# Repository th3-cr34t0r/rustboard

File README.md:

# RUSTBOARD

- Rust based firmware for split keyboards

## About:
- Initially started as an ESP32 project, being build for fun and learning embedded rust.

## Features:
- Supporting bluetooth
- Supporting split keyboards
- Layers
- Combos

## Current bugs:
- Unable to remember paired devices

## How to compile:
- cargo build --release --features central / peripheral

### To build uf2 firmware:
- cargo make uf2 --release

- The above command will generate 2 .uf2 file, one peripheral one central, that can be drag and dropped to the bootloader

## TODO:
- [ ] Central connection to be improved - (kinda improved it, need to turn on the central split, then the peripheral in order to connect correctly)
- [ ] Improve central device connection (scan for avalible devices, check for vendor id, name, charactersitics that match the peripheral, then connect (no specifying of the peripherals ble address))
- [ ] Introduce macros feature
- [ ] Introduce sleep
- [ ] Finish up implementing user_config.toml configuration
- [ ] Make esp32 compatible
- [ ] Write detailed documentation on how to set up
- [ ] UI for configuration?
- [ ] Clear stored BLE pairing informtaion on a key combo / keypress for several seconds
- [ ] Improve combos feature setup

- [X] ~~Improve latency~~
- [X] ~~Share central battery level with peripheral, show the lower value to the connected device~~ - done (although on samo nrf52 clones, looks like the pin is not the correct one)
- [X] ~~Enter bootloader more easily~~ - bootloader is entered when key row:0, col:0 is held and released after 5s
- [X]  ~~Introduce combos feature~~ - done 
- [X]  ~~Solder battery and a power-switch~~ - done 
- [X]  ~~Battery level readings (saadc) feature~~ - done
- [X]  ~~Introduce a debounce feature for the matrix (sometimes with the current approach, some keys are registered 2 times)~~ - done

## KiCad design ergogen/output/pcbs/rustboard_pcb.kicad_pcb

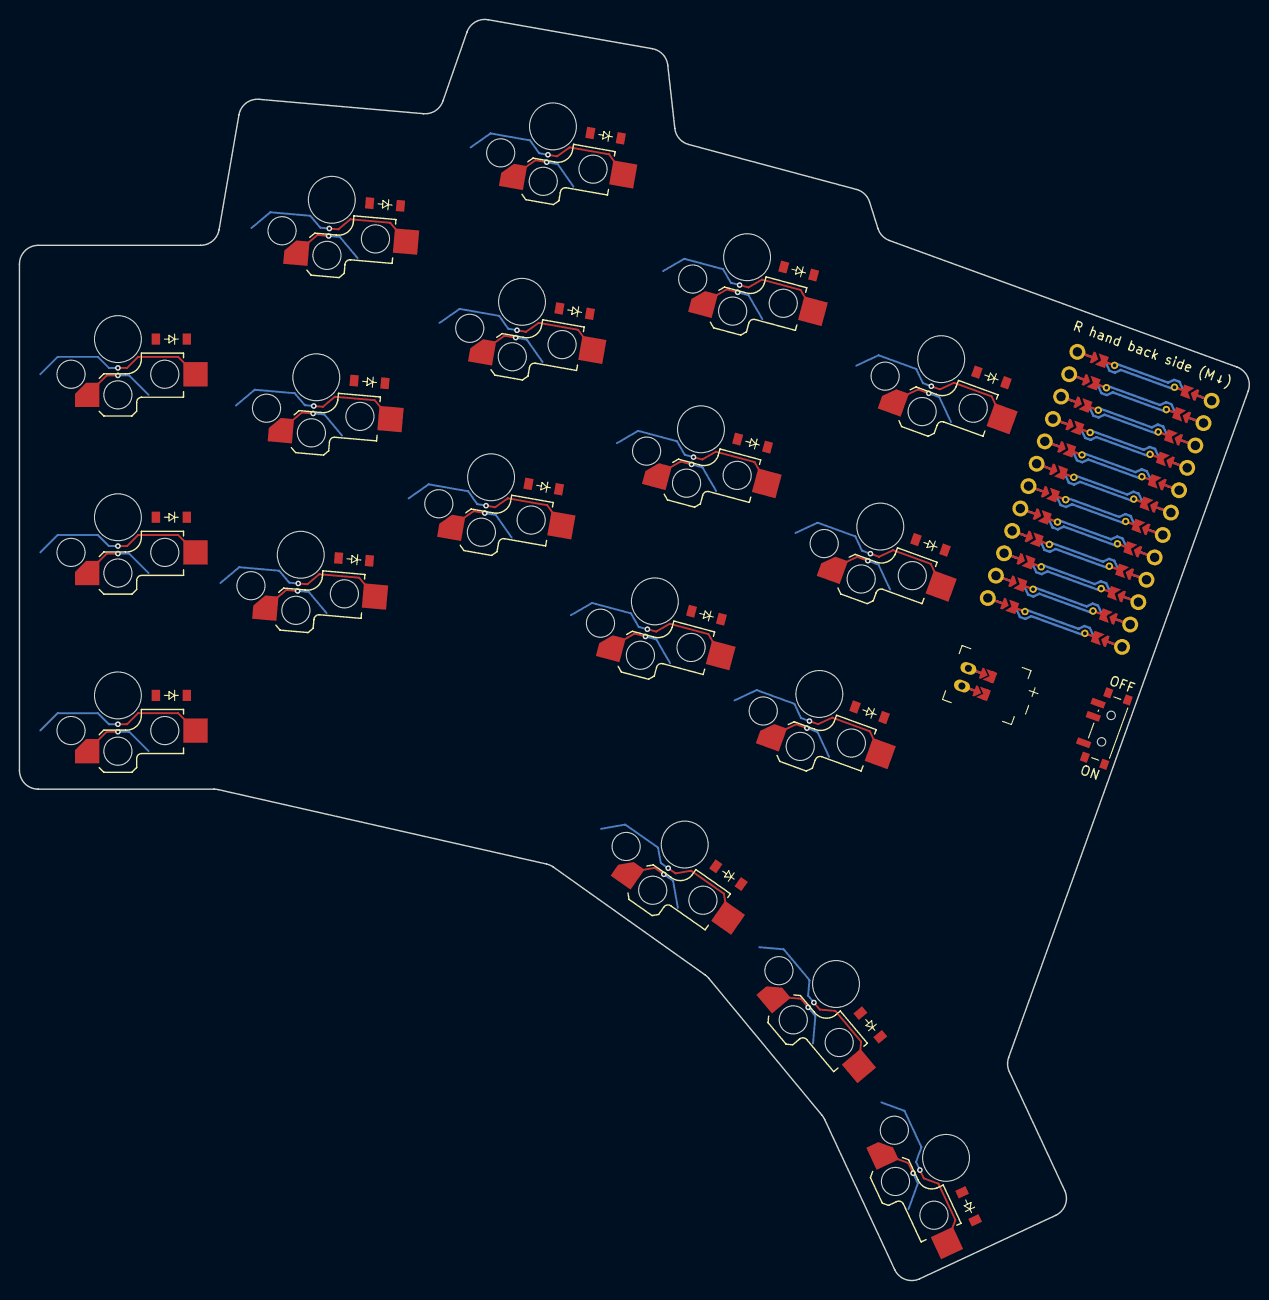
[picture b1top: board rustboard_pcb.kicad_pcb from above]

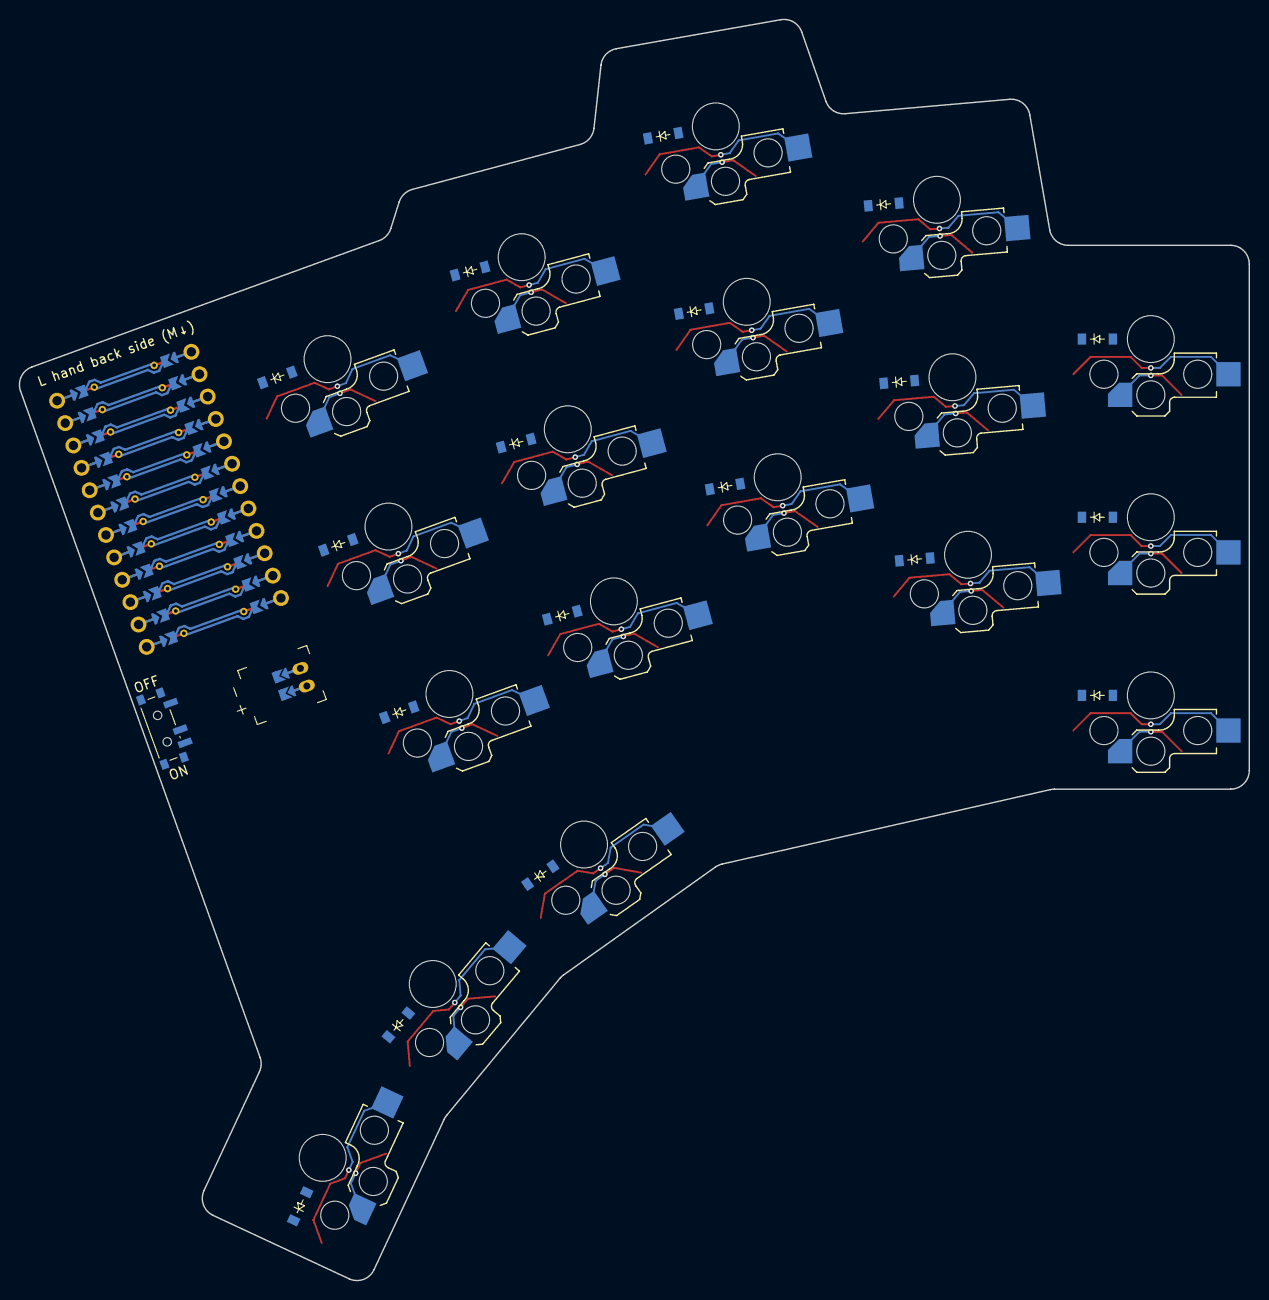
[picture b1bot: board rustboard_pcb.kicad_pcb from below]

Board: 2 copper layers, 131.2 x 134.5 mm, 39 parts (18 on the bottom side), 33 nets.

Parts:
D1, D2, D3, D4, D5, D6, D7, D8, D9, D10, D11, D12, D13, D14, D15, D16, D17, D18: diode_tht_sod123
JST1: battery_connector_jst_ph_2
MCU1: mcu_nice_nano
PWR1: power_switch_smd_side
S1, S2, S3, S4, S5, S6, S7, S8, S9, S10, S11, S12, S13, S14, S15, S16, S17, S18: switch_choc_v1_v2

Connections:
B+: MCU1.101, PWR1.2
BAT_P: JST1.1, PWR1.1, PWR1.3
GND: JST1.2, MCU1.103, MCU1.120
JST1_1: JST1.11, JST1.21, JST1.31
JST1_2: JST1.12, JST1.22, JST1.32
P002: MCU1.108, S7.2, S8.2, S9.2, S16.2
P017: D3.1, D6.1, D9.1, D12.1, D15.1, MCU1.119
P020: D2.1, D5.1, D8.1, D11.1, D14.1, MCU1.118
P022: D1.1, D4.1, D7.1, D10.1, D13.1, MCU1.117
P024: D16.1, D17.1, D18.1, MCU1.116
P029: MCU1.107, S4.2, S5.2, S6.2
P031: MCU1.106, S1.2, S2.2, S3.2
P113: MCU1.110, S13.2, S14.2, S15.2, S18.2
P115: MCU1.109, S10.2, S11.2, S12.2, S17.2
RAW: MCU1.102, MCU1.121, MCU1.122
c0_r0: D3.2, S3.1
c0_r1: D2.2, S2.1
c0_r2: D1.2, S1.1
c1_r0: D6.2, S6.1
c1_r1: D5.2, S5.1
c1_r2: D4.2, S4.1
c2_r0: D9.2, S9.1
c2_r1: D8.2, S8.1
c2_r2: D7.2, S7.1
c2_r3: D16.2, S16.1
c3_r0: D12.2, S12.1
c3_r1: D11.2, S11.1
c3_r2: D10.2, S10.1
c3_r3: D17.2, S17.1
c4_r0: D15.2, S15.1
c4_r1: D14.2, S14.1
c4_r2: D13.2, S13.1
c4_r3: D18.2, S18.1

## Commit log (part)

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2026-01-30 created rustboard macros for generating input and output pins based on user config toml file
2026-02-02 reorg
2026-02-02 fix .gitignore
2026-02-02 target removed
2026-02-03 revert macros, added conn param update
2026-02-06 removed extra service in hid advertise, moved keymap to config file
2026-02-15 reverted to old hid descriptor, more compatible with other PCs
2026-02-15 updated layout so entering bootloader is possible
2026-02-15 added debug info for bond value
2026-02-15 config for creamy purple pro kb
2026-02-16 bumped trouble version
2026-02-16 fixed average value calculation
2026-02-16 adapted for trouble v0.6
2026-02-21 New todo
2026-02-21 better readability
2026-04-12 ergogen + kicad
2026-04-14 ide ignore kicad, ergogen
2026-04-14 fix layer handling
2026-04-15 code adapted to PubSubChannel
2026-04-15 swapped Watch with PubSubChannel
2026-04-15 moved async interrupt logic to struct method, naming cleaned, interrupt now waits for high instead of any_edge
2026-04-15 removed whole method, naming simplified for some vars, overall cleanup
2026-04-29 cycle optimization, layer logic fixed, binary optimizations added
